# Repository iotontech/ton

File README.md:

Ton V1.2
========

The Ton V1.2 Board is a development and prototyping platform with Bluetooth Low Energy, Wi-Fi and IMU 9-axis,
based on the ARM Cortex-M4 32-bit microcontroller [STM32F405](http://www.st.com/web/en/catalog/mmc/SC1169/SS1577/LN1035/PF252144) developed by Brazilian startup [IOTON Technology](http://ioton.cc/).

# License

Copyright IOTON Technology 2017.

This documentation describes Open Hardware and is licensed under the CERN OHL v. 1.2.
You may redistribute and modify this documentation under the terms of the CERN OHL v.1.2. (http://ohwr.org/cernohl). This documentation is distributed WITHOUT ANY EXPRESS OR IMPLIED WARRANTY, INCLUDING OF MERCHANTABILITY, SATISFACTORY QUALITY AND FITNESS FOR A PARTICULAR PURPOSE. Please see the CERN OHL v.1.2 for applicable conditions.

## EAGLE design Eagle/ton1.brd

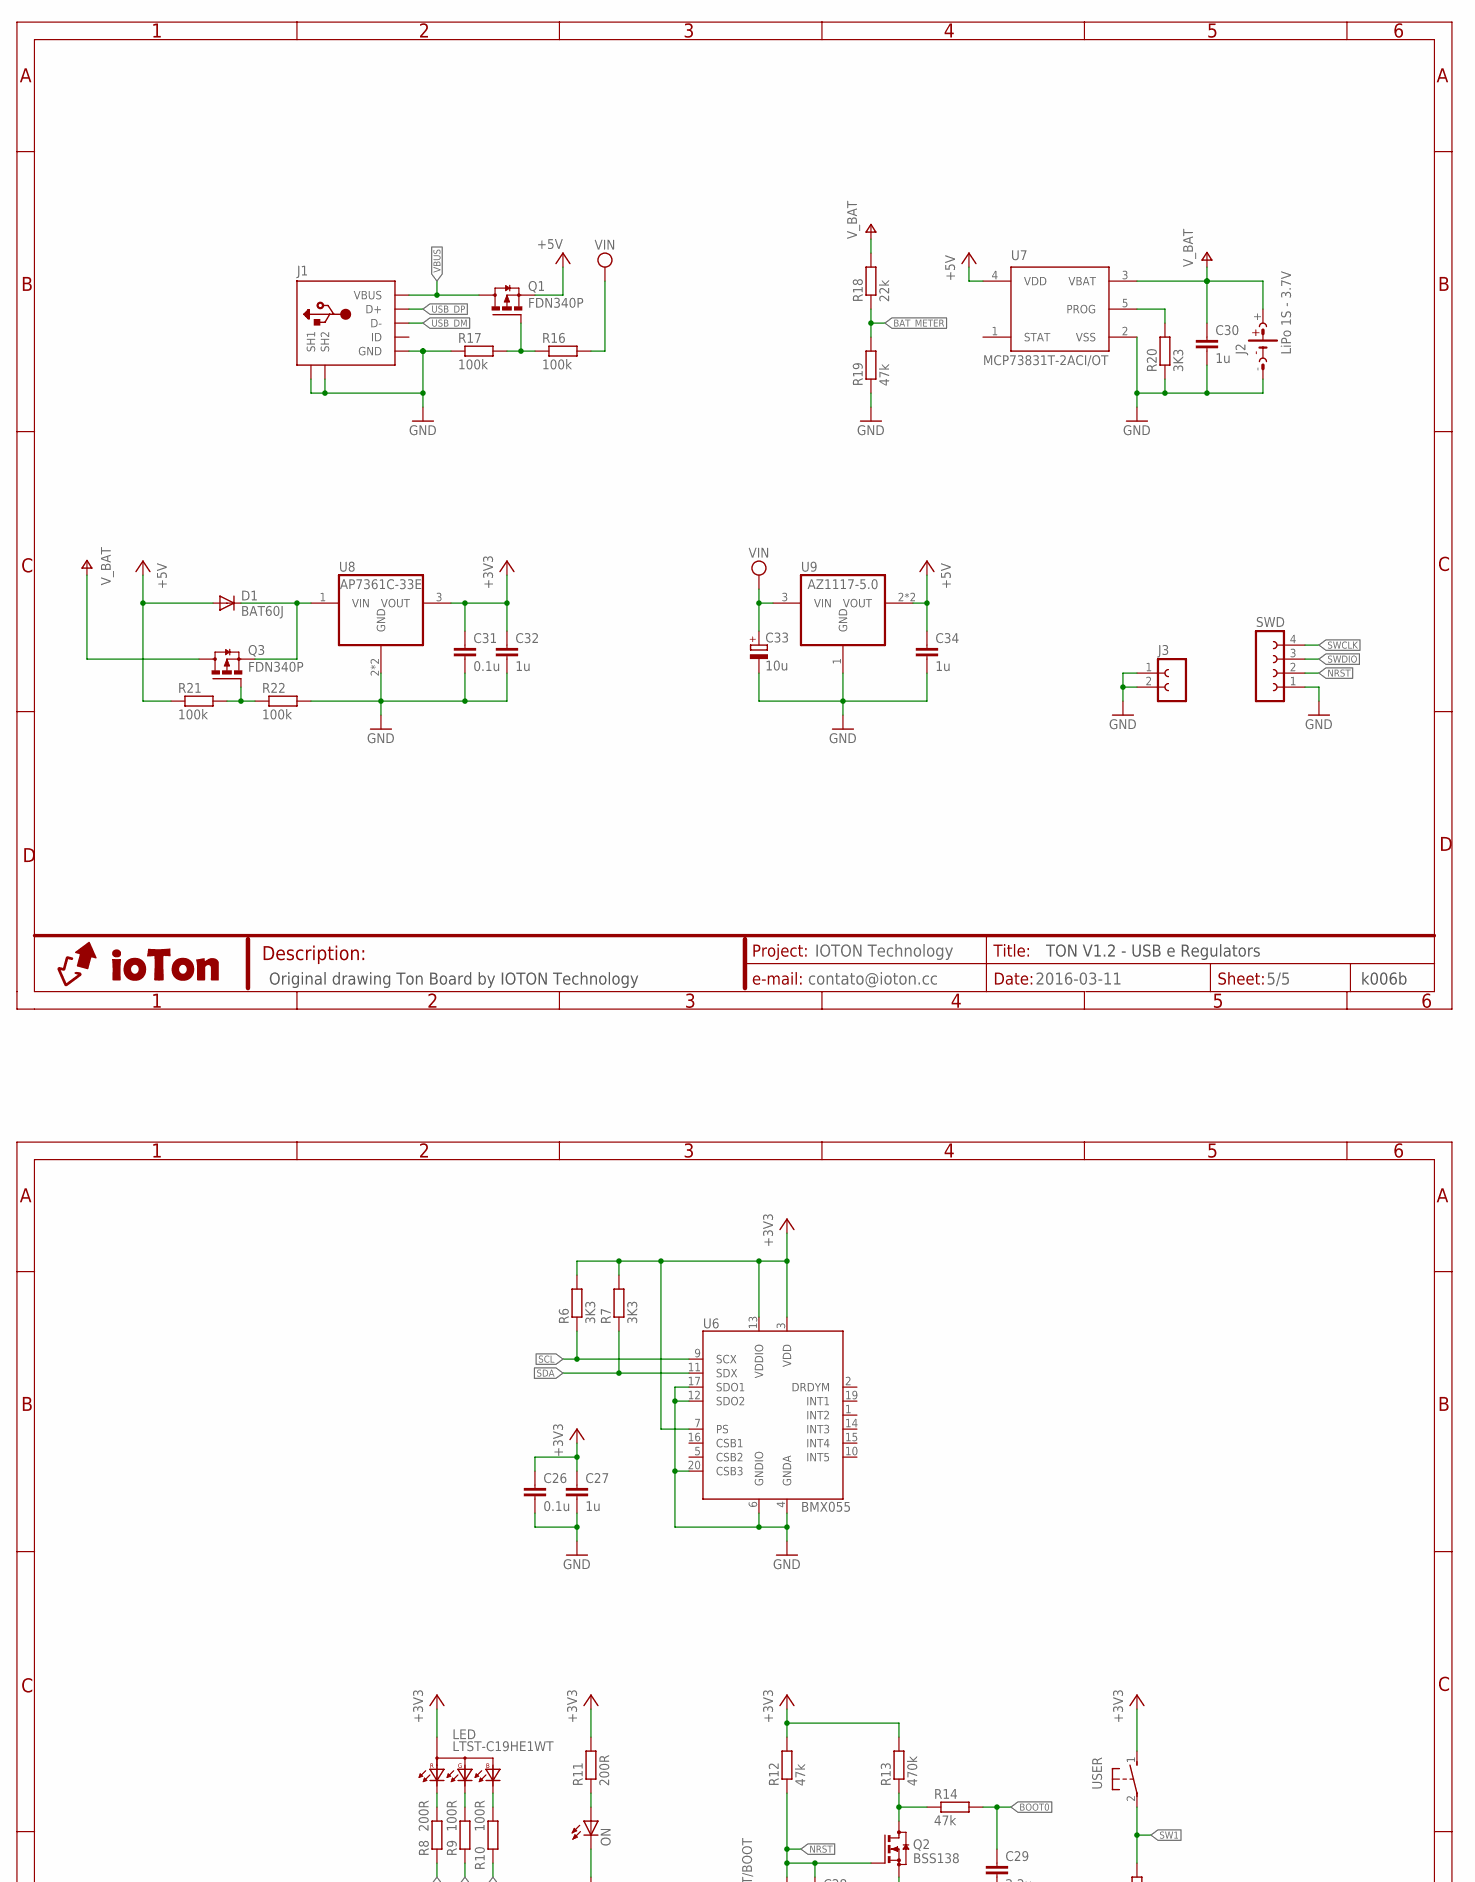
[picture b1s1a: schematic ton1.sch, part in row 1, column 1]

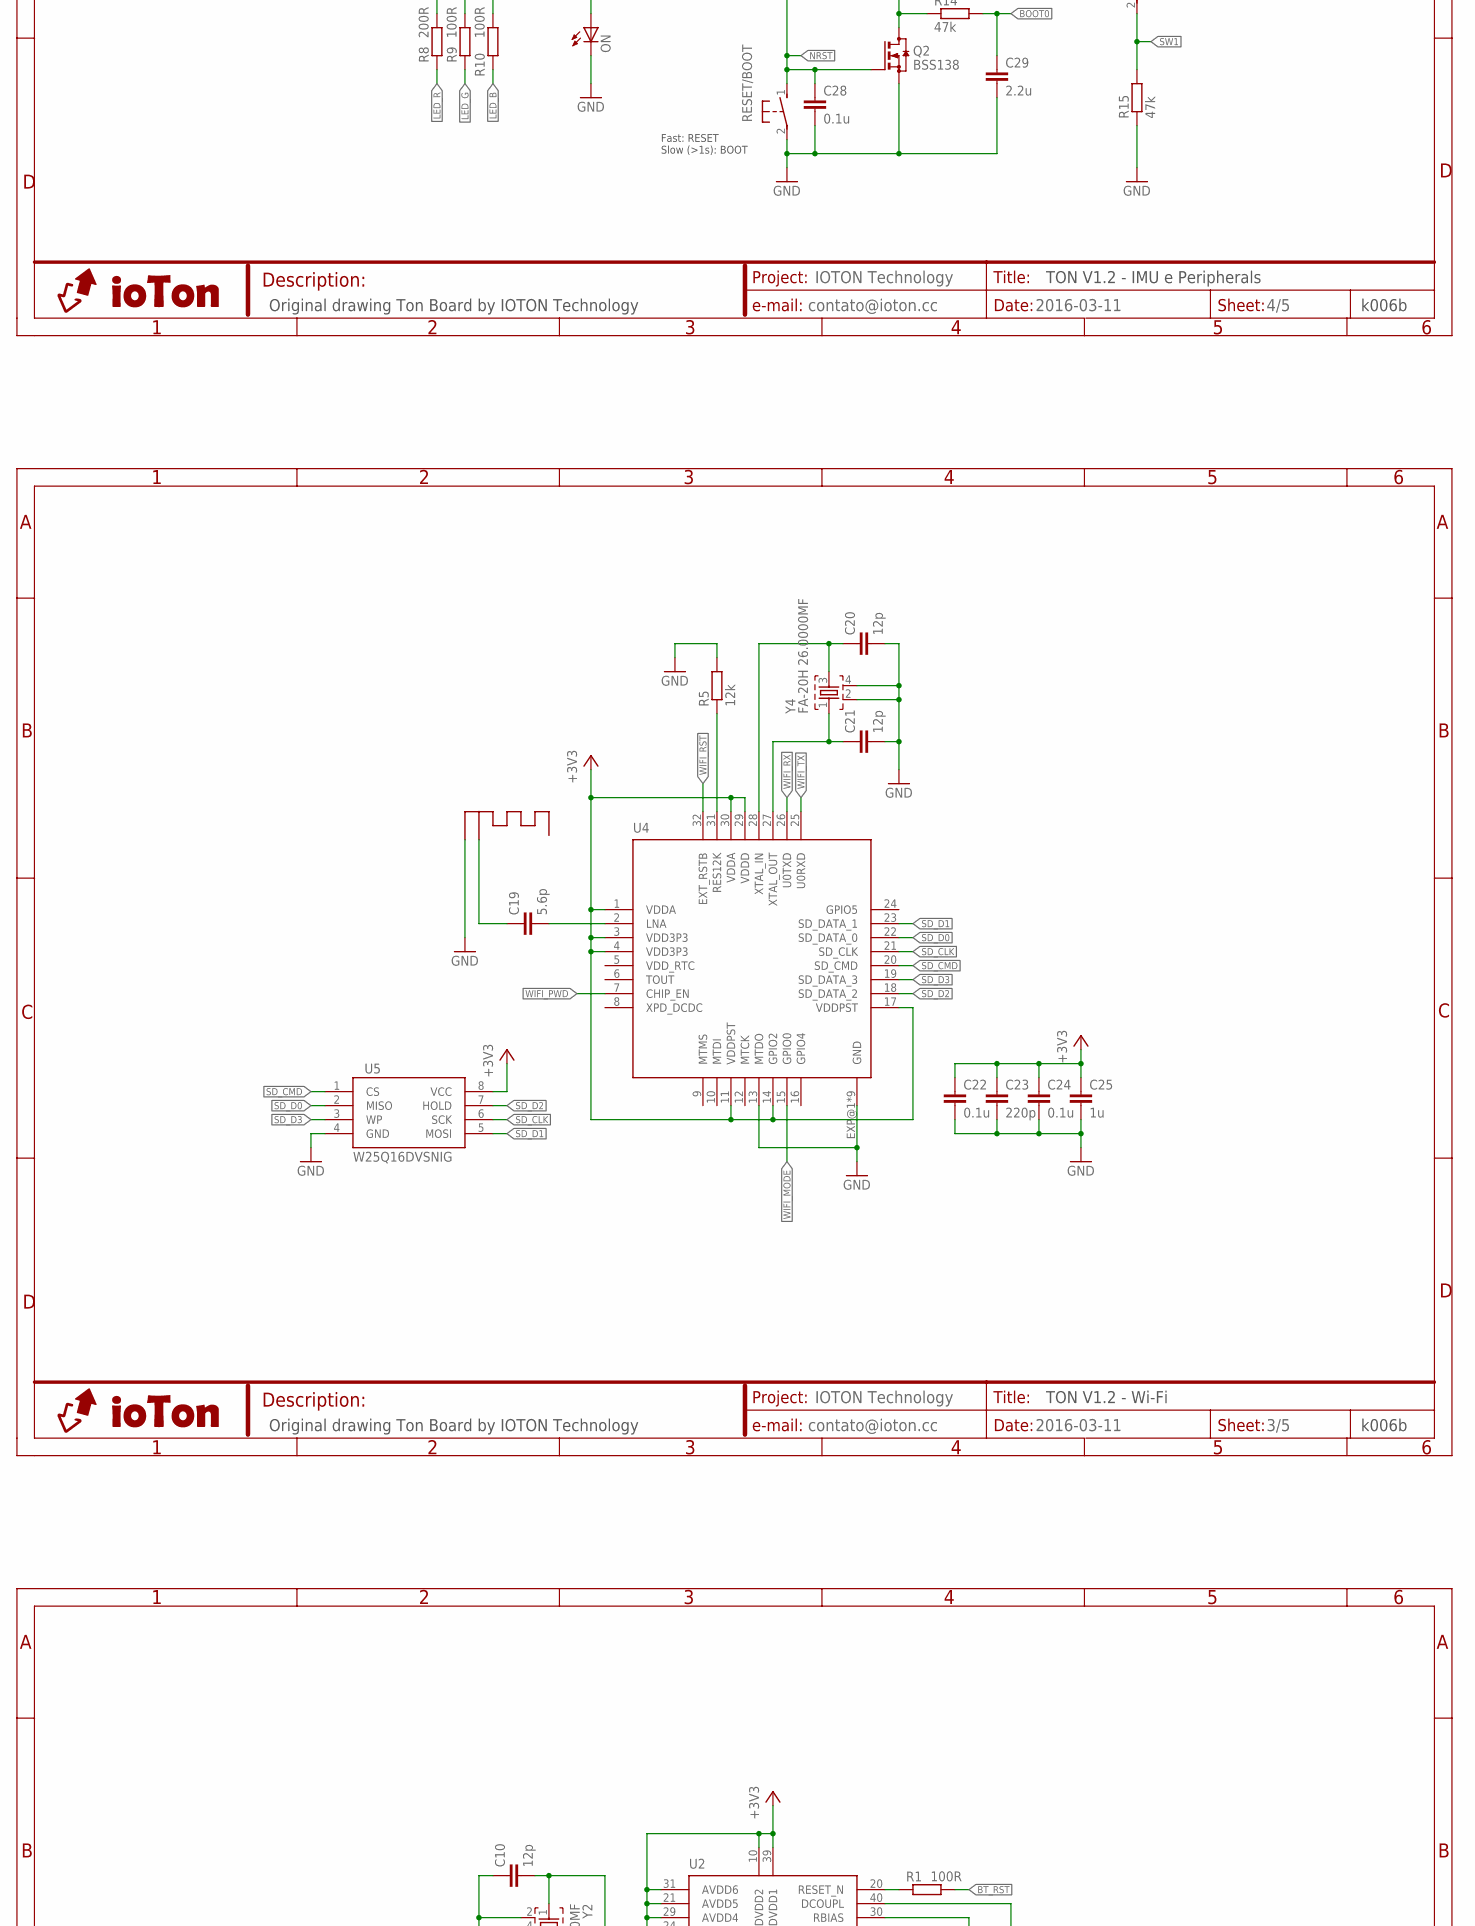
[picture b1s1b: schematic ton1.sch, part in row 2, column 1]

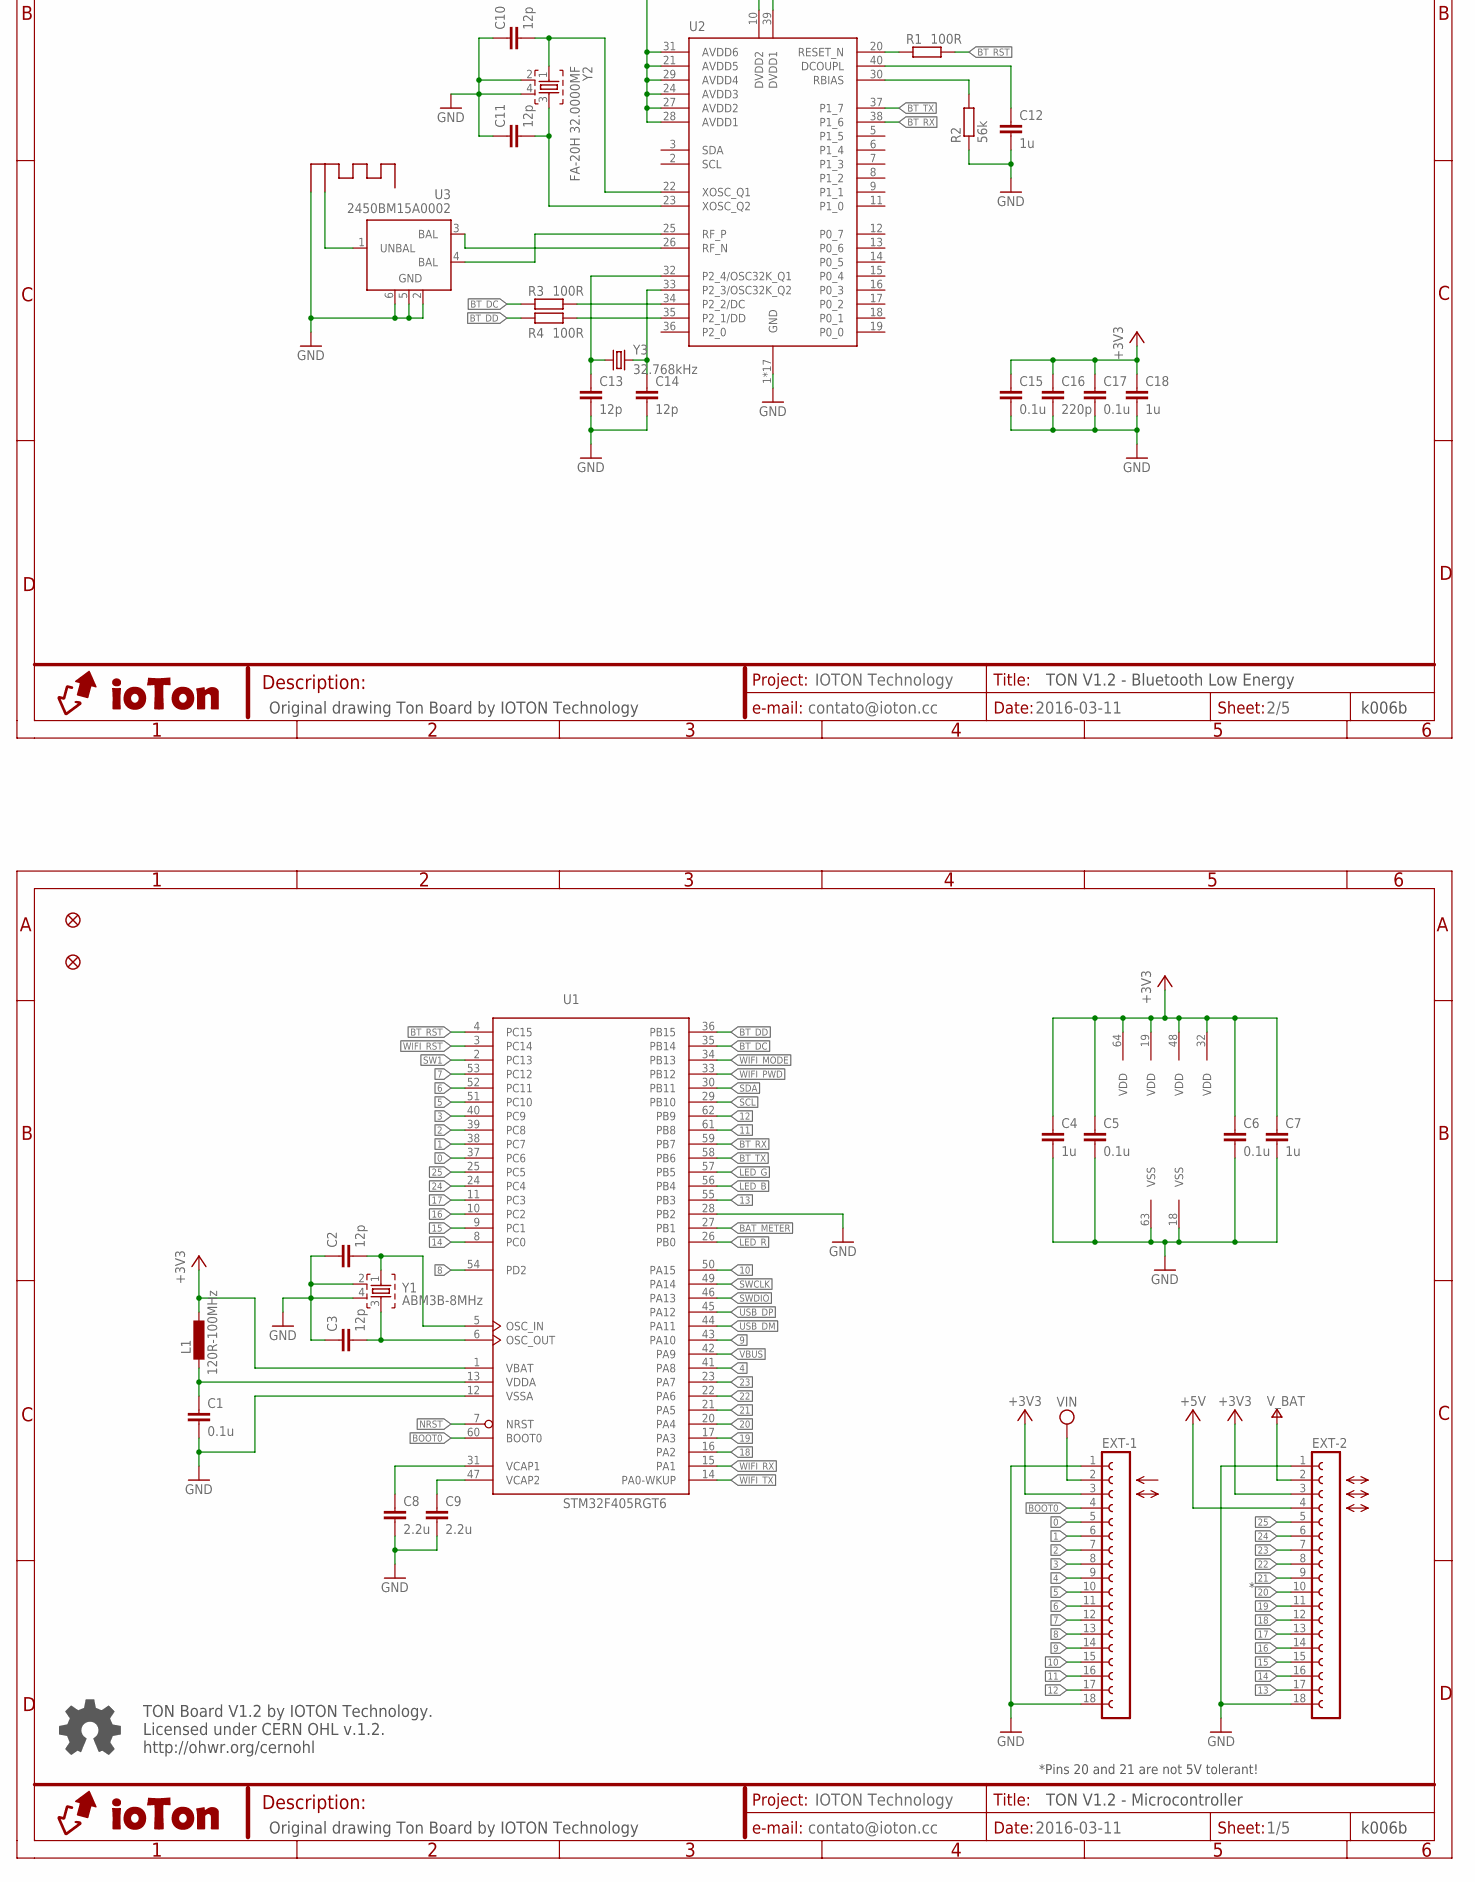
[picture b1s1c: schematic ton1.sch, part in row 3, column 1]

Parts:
C1, C5, C6, C26, C28, C31: 0.1u; C0603
C2, C3, C10, C11, C13, C14, C20, C21: 12p; C0402
C4, C7, C27, C30, C32, C34: 1u; C0603
C8, C9, C29: 2.2u; C0603
C12, C18, C25: 1u; C0402
C15, C17, C22, C24: 0.1u; C0402
C16, C23: 220p; C0402
C19: 5.6p; C0402
C33: 10u; SMC_A
D1: BAT60J; SOD323-R
EXT-1, EXT-2: 1_18
J1: USBR; 0475890001
J2: LiPo 1S - 3.7V; BATTERY
J3: 1_2
JP1, JP2: FIDUCIAL1X2; FIDUCIAL-1X2
L1: 120R-100MHz; LR0603
LED: LTST-C19HE1WT; 0606
ON: LEDCHIPLED_0603; CHIPLED_0603
Q1, Q3: FDN340P; SUPER-SOT3
Q2: BSS138; SOT23
R1, R3, R4: 100R; R0402
R2: 56k; R0402
R5: 12k; R0402
R6, R7, R20: 3K3; R0603
R8, R11: 200R; R0603
R9, R10: 100R; R0603
R12, R14, R15, R19: 47k; R0603
R13: 470k; R0603
R16, R17, R21, R22: 100k; R0603
R18: 22k; R0603
RESET/BOOT: SWITCH; SW_TL-3330
SWD: FE04-11; CON4-1_1
U1: STM32F405RGT6; LQFP64
U2: CC2541; QFN40-6X6
U3: 2450BM15A0002
U4: ESP8266O; QFN32-5X5-O
U5: W25Q16DVSNIG; SO08
U6: BMX055; LGA20-4.5X3
U7: MCP73831T-2ACI/OT; SOT23-5L
U8: AP7361C-33E; SOT223
U9: AZ1117-5.0; SOT223
U$1: ANT_PCBR; ANT_MIFA_R
U$2: ANT_PCBL; ANT_MIFA_L
USER: SWITCH; SW_TL-3330
Y1: ABM3B-8MHz; ABM3B
Y2: FA-20H 32.0000MF; FA-20H
Y3: 32.768kHz; 3.2X1.5
Y4: FA-20H 26.0000MF; FA-20H

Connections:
0: EXT-1.5, U1.37 (PC6)
1: EXT-1.6, U1.38 (PC7)
2: EXT-1.7, U1.39 (PC8)
3: EXT-1.8, U1.40 (PC9)
4: EXT-1.9, U1.41 (PA8)
5: EXT-1.10, U1.51 (PC10)
6: EXT-1.11, U1.52 (PC11)
7: EXT-1.12, U1.53 (PC12)
8: EXT-1.13, U1.54 (PD2)
9: EXT-1.14, U1.43 (PA10)
10: EXT-1.15, U1.50 (PA15)
11: EXT-1.16, U1.61 (PB8)
12: EXT-1.17, U1.62 (PB9)
13: EXT-2.17, U1.55 (PB3)
14: EXT-2.16, U1.8 (PC0)
15: EXT-2.15, U1.9 (PC1)
16: EXT-2.14, U1.10 (PC2)
17: EXT-2.13, U1.11 (PC3)
18: EXT-2.12, U1.16 (PA2)
19: EXT-2.11, U1.17 (PA3)
20: EXT-2.10, U1.20 (PA4)
21: EXT-2.9, U1.21 (PA5)
22: EXT-2.8, U1.22 (PA6)
23: EXT-2.7, U1.23 (PA7)
24: EXT-2.6, U1.24 (PC4)
25: EXT-2.5, U1.25 (PC5)
+3V3: C4.1, C5.1, C6.1, C7.1, C15.1, C16.1, C17.1, C18.1, C22.1, C23.1, C24.1, C25.1, C26.1, C27.1, C31.1, C32.1, EXT-1.3, EXT-2.3, L1.2, LED.4 (A), R6.2, R7.2, R11.2, R12.2, R13.2, U1.1 (VBAT), U1.19 (VDD), U1.32 (VDD), U1.48 (VDD), U1.64 (VDD), U2.10 (DVDD2), U2.21 (AVDD5), U2.24 (AVDD3), U2.27 (AVDD2), U2.28 (AVDD1), U2.29 (AVDD4), U2.31 (AVDD6), U2.39 (DVDD1), U4.1 (VDDA), U4.3 (VDD3P3), U4.4 (VDD3P3), U4.11 (VDDPST), U4.14 (GPIO2), U4.17 (VDDPST), U4.29 (VDDD), U4.30 (VDDA), U5.8 (VCC), U6.3 (VDD), U6.7 (PS), U6.13 (VDDIO), U8.3 (VOUT), USER.1
+5V: C34.1, D1.A, EXT-2.4, Q1.2 (S), R21.1, U7.4 (VDD), U9.2 (VOUT), U9.4 (VOUT)
BAT_METER: R18.1, R19.2, U1.27 (PB1)
BOOT0: C29.1, EXT-1.4, R14.2, U1.60 (BOOT0)
BT_ANT: U3.1 (UNBAL), U$2.ANT
BT_DC: R3.1, U1.35 (PB14)
BT_DD: R4.1, U1.36 (PB15)
BT_RST: R1.2, U1.4 (PC15)
BT_RX: U1.59 (PB7), U2.38 (P1_6)
BT_TX: U1.58 (PB6), U2.37 (P1_7)
GND: C1.2, C2.1, C3.1, C4.2, C5.2, C6.2, C7.2, C8.2, C9.2, C10.1, C11.1, C12.2, C13.2, C14.2, C15.2, C16.2, C17.2, C18.2, C20.2, C21.2, C22.2, C23.2, C24.2, C25.2, C26.2, C27.2, C28.2, C29.2, C30.2, C31.2, C32.2, C33.-, C34.2, EXT-1.1, EXT-1.18, EXT-2.1, EXT-2.18, J1.5 (GND), J1.SH1, J1.SH2 (SH1), J1.SH3 (SH2), J1.SH4 (SH2), J1.SH5 (SH1), J1.SH6 (SH2), J2.-, J3.1, J3.2, ON.C, Q2.2 (S), R2.1, R5.2, R15.1, R17.1, R19.1, R20.1, R22.2, RESET/BOOT.2, SWD.1, U1.12 (VSSA), U1.18 (VSS), U1.28 (PB2), U1.63 (VSS), U2.1 (GND), U2.EXP@1 (GND), U2.EXP@2 (GND), U2.EXP@3 (GND), U2.EXP@4 (GND), U2.EXP@5 (GND), U2.EXP@6 (GND), U2.EXP@7 (GND), U2.EXP@8 (GND), U2.EXP@9 (GND), U2.EXP@10 (GND), U2.EXP@11 (GND), U2.EXP@12 (GND), U2.EXP@13 (GND), U2.EXP@14 (GND), U2.EXP@15 (GND), U2.EXP@16 (GND), U3.2 (GND), U3.5 (GND), U3.6 (GND), U4.13 (MTDO), U4.EXP@1 (GND), U4.EXP@2 (GND), U4.EXP@3 (GND), U4.EXP@5 (GND), U4.EXP@6 (GND), U4.EXP@7 (GND), U4.EXP@9 (GND), U4.EXP@10 (GND), U4.EXP@11 (GND), U5.4 (GND), U6.4 (GNDA), U6.6 (GNDIO), U6.12 (SDO2), U6.17 (SDO1), U6.20 (CSB3), U7.2 (VSS), U8.2 (GND), U8.4 (GND), U9.1 (GND), U$1.GND, U$2.GND, Y1.2, Y1.4, Y2.2, Y2.4, Y4.2, Y4.4
LED_B: R10.1, U1.56 (PB4)
LED_G: R9.1, U1.57 (PB5)
LED_R: R8.1, U1.26 (PB0)
unnamed: C2.2, U1.5 (OSC_IN), Y1.1
unnamed: C3.2, U1.6 (OSC_OUT), Y1.3
unnamed: C13.1, U2.32 (P2_4/OSC32K_Q1), Y3.1
unnamed: LED.1 (KRED), R8.2
unnamed: C8.1, U1.31 (VCAP1)
unnamed: C9.1, U1.47 (VCAP2)
unnamed: LED.2 (KGREEN), R9.2
unnamed: LED.3 (KBLUE), R10.2
unnamed: C1.1, L1.1, U1.13 (VDDA)
unnamed: R5.1, U4.31 (RES12K)
unnamed: C21.1, U4.27 (XTAL_OUT), Y4.1
unnamed: U2.26 (RF_N), U3.3 (BAL)
unnamed: R2.2, U2.30 (RBIAS)
unnamed: C12.1, U2.40 (DCOUPL)
unnamed: U2.25 (RF_P), U3.4 (BAL)
unnamed: R3.2, U2.34 (P2_2/DC)
unnamed: C20.1, U4.28 (XTAL_IN), Y4.3
unnamed: R20.2, U7.5 (PROG)
unnamed: C10.2, U2.22 (XOSC_Q1), Y2.1
unnamed: C11.2, U2.23 (XOSC_Q2), Y2.3
unnamed: R4.2, U2.35 (P2_1/DD)
unnamed: R1.1, U2.20 (RESET_N)
unnamed: C19.2, U4.2 (LNA)
unnamed: C14.1, U2.33 (P2_3/OSC32K_Q2), Y3.2
unnamed: ON.A, R11.1
unnamed: Q1.1 (G), R16.1, R17.2
unnamed: Q2.3 (D), R13.1, R14.1
unnamed: Q3.1 (G), R21.2, R22.1
NRST: C28.1, Q2.1 (G), R12.1, RESET/BOOT.1, SWD.2, U1.7 (NRST)
SCL: R6.1, U1.29 (PB10), U6.9 (SCX)
SDA: R7.1, U1.30 (PB11), U6.11 (SDX)
SD_CLK: U4.21 (SD_CLK), U5.6 (SCK)
SD_CMD: U4.20 (SD_CMD), U5.1 (CS)
SD_D0: U4.22 (SD_DATA_0), U5.2 (MISO)
SD_D1: U4.23 (SD_DATA_1), U5.5 (MOSI)
SD_D2: U4.18 (SD_DATA_2), U5.7 (HOLD)
SD_D3: U4.19 (SD_DATA_3), U5.3 (WP)
SW1: R15.2, U1.2 (PC13), USER.2
SWCLK: SWD.4, U1.49 (PA14)
SWDIO: SWD.3, U1.46 (PA13)
USB_DM: J1.2 (D-), U1.44 (PA11)
USB_DP: J1.3 (D+), U1.45 (PA12)
V+: C30.1, EXT-2.2, J2.+, Q3.3 (D), R18.2, U7.3 (VBAT)
VBUS: J1.1 (VBUS), Q1.3 (D), U1.42 (PA9)
VDD_RTC: U4.5 (VDD_RTC)
VIN_3V3: D1.C, Q3.2 (S), U8.1 (VIN)
VPP: C33.+, EXT-1.2, R16.2, U9.3 (VIN)
WIFI_ANT: C19.1, U$1.ANT
WIFI_MODE: U1.34 (PB13), U4.15 (GPIO0)
WIFI_PWD: U1.33 (PB12), U4.7 (CHIP_EN)
WIFI_RST: U1.3 (PC14), U4.32 (EXT_RSTB)
WIFI_RX: U1.15 (PA1), U4.26 (U0TXD)
WIFI_TX: U1.14 (PA0-WKUP), U4.25 (U0RXD)

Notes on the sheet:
TON V1.2 - Microcontroller
TON V1.2 - Bluetooth Low Energy
TON V1.2 - Wi-Fi
TON V1.2 - IMU e Peripherals
TON V1.2 - USB e Regulators
TON Board V1.2 by IOTON Technology. Licensed under CERN OHL v.1.2. http://ohwr.org/cernohl
Original drawing Ton Board by IOTON Technology
k006b
*Pins 20 and 21 are not 5V tolerant!
Fast: RESET Slow (>1s): BOOT

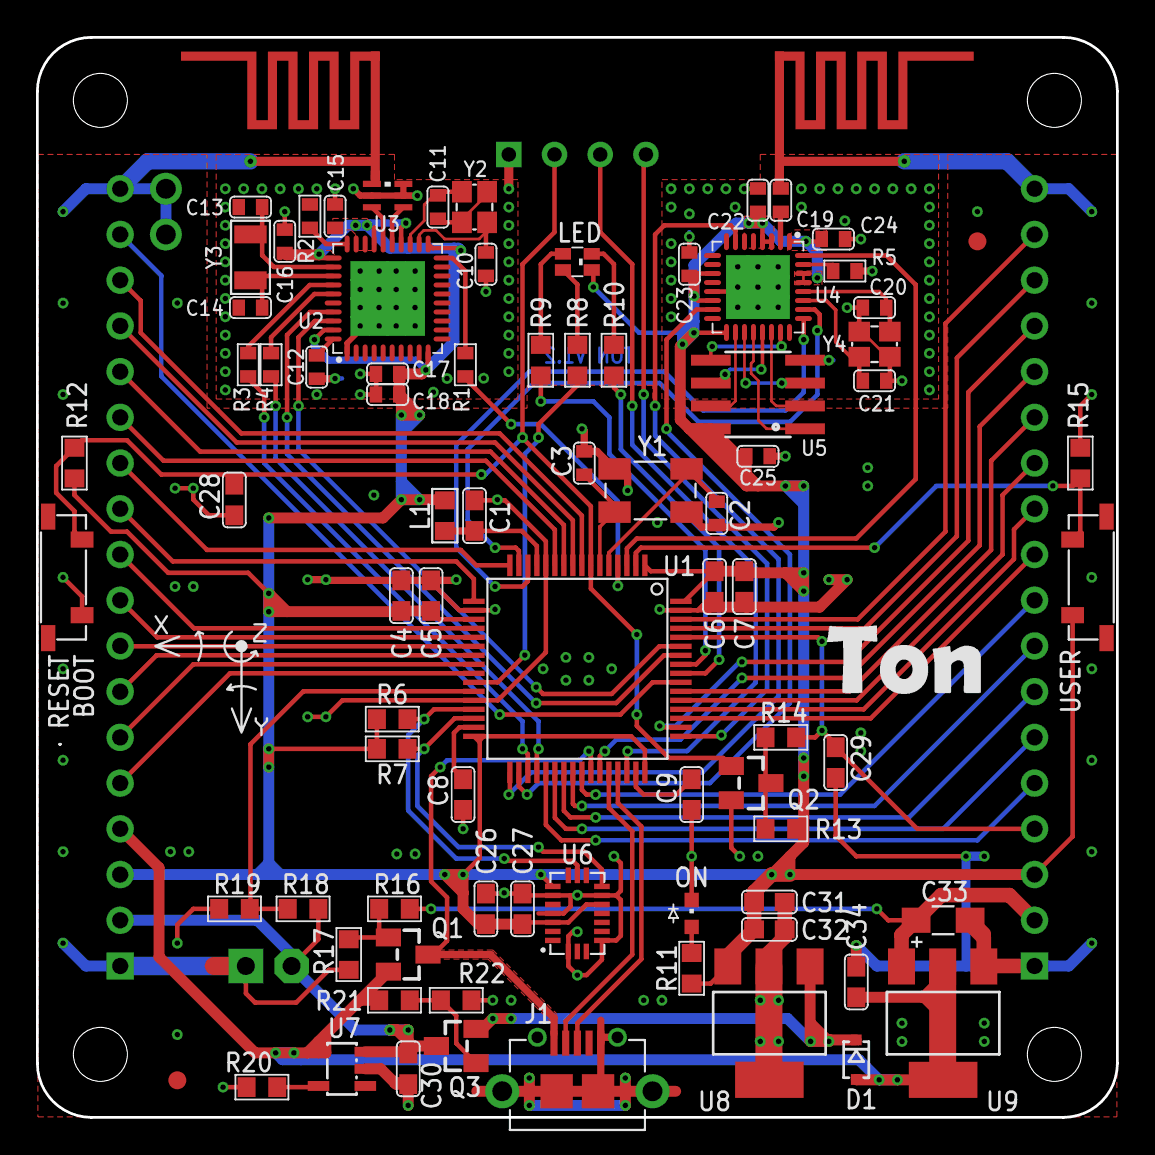
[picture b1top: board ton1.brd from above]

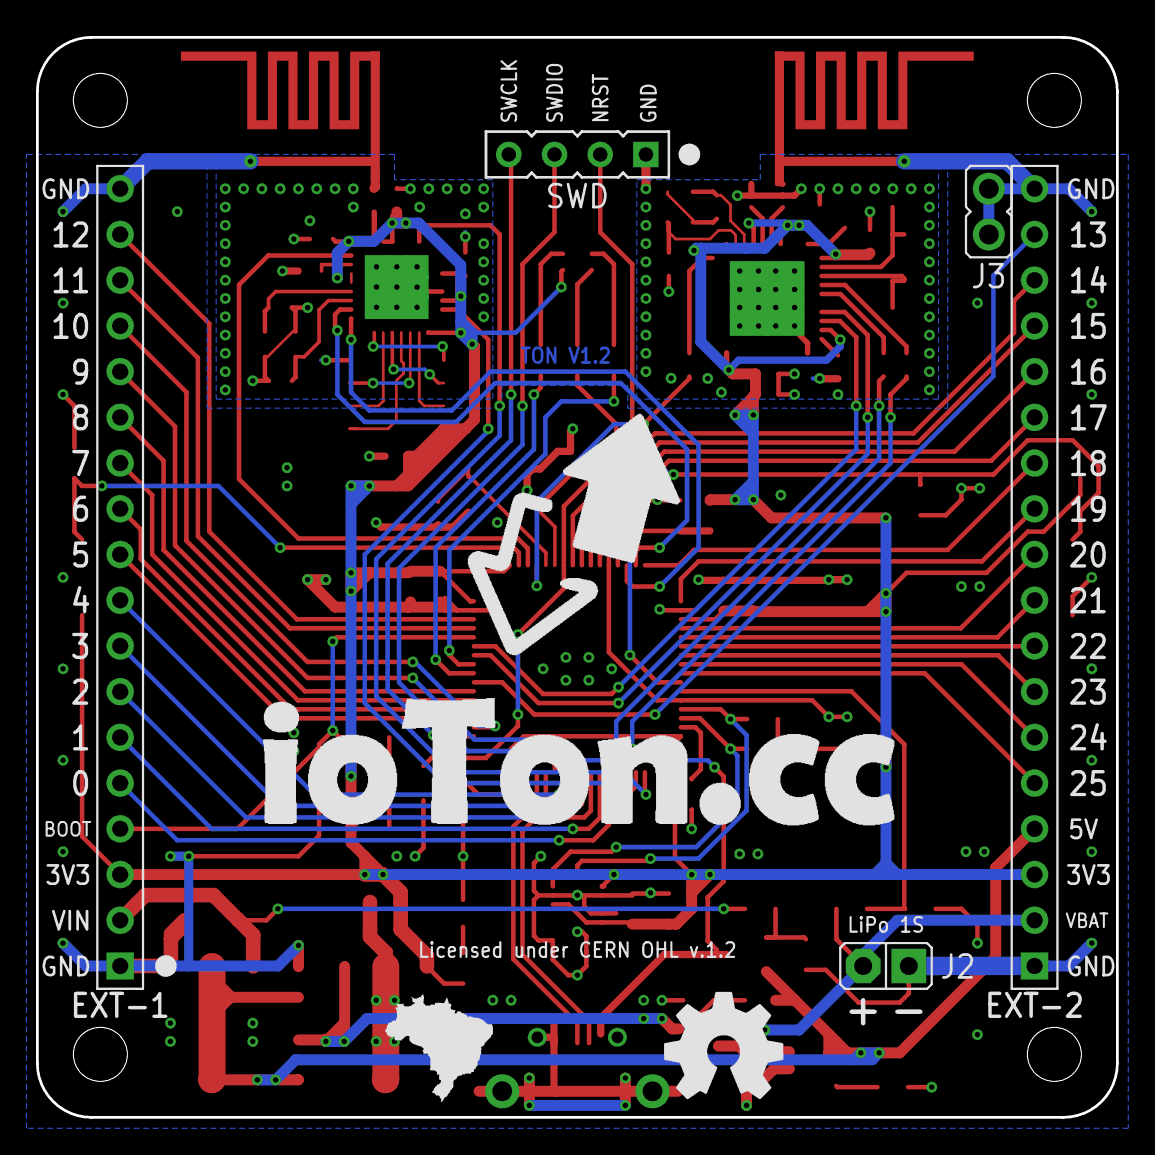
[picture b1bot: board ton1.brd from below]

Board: 2 copper layers, 60.0 x 60.0 mm, 88 parts (5 on the bottom side), 92 nets.

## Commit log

2017-02-21 First commit - Release v1.2.0
2017-02-21 Fix Readme image path
2017-02-21 Fix Manual path (old links)

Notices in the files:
parts and their libraries:
SparkFun: Licensing: CC v3.0 Share-Alike You are welcome to use this library for commercial purposes.
